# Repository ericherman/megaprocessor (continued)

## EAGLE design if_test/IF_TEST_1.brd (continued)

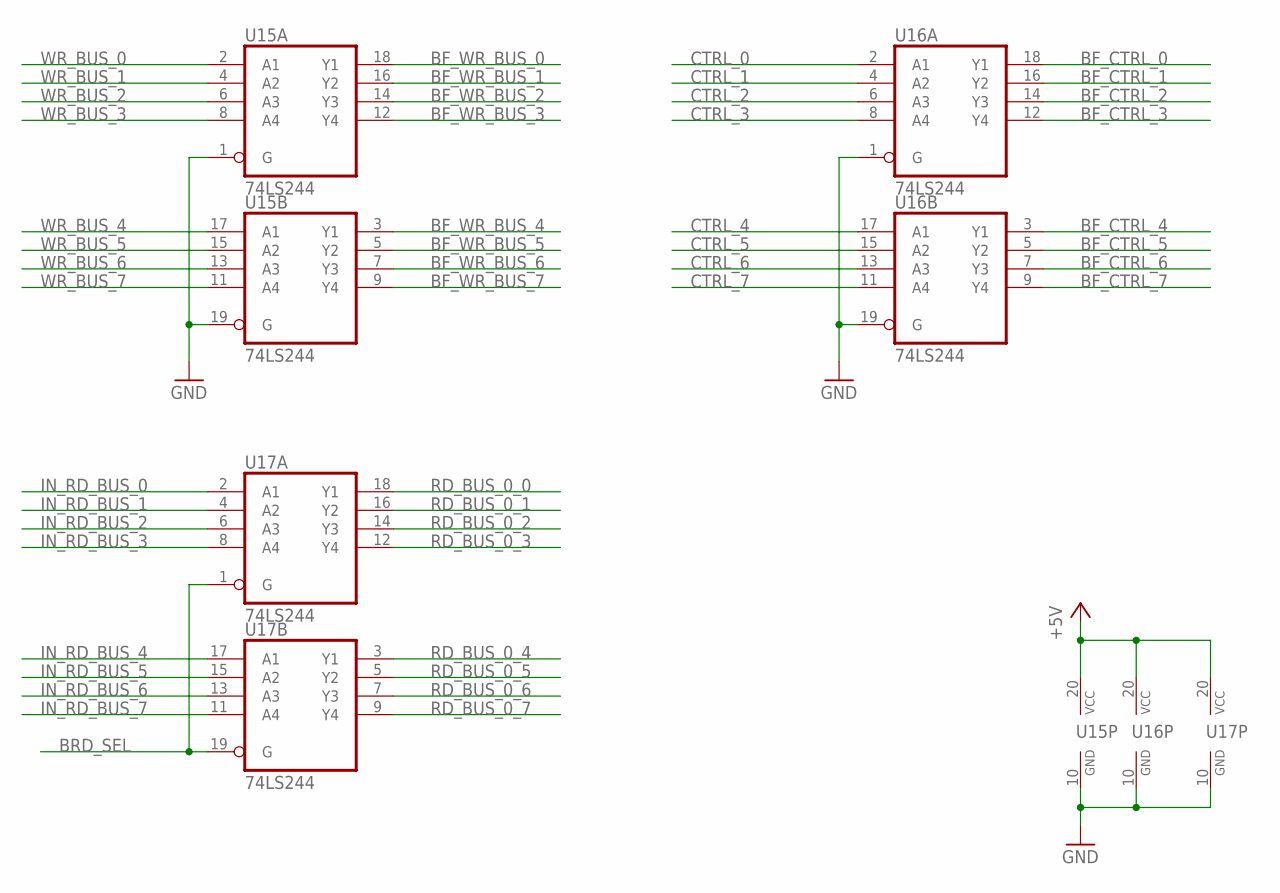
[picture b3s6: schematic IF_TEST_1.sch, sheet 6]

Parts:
U15, U16, U17: 74LS244; DIP20

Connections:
+5V: U15.20 (VCC), U16.20 (VCC), U17.20 (VCC); also elsewhere on the board
BF_CTRL_0: U16.18 (Y1); also elsewhere on the board
BF_CTRL_1: U16.16 (Y2); also elsewhere on the board
BF_CTRL_2: U16.14 (Y3); also elsewhere on the board
BF_CTRL_3: U16.12 (Y4); also elsewhere on the board
BF_CTRL_4: U16.3 (Y1); also elsewhere on the board
BF_CTRL_5: U16.5 (Y2); also elsewhere on the board
BF_CTRL_6: U16.7 (Y3); also elsewhere on the board
BF_CTRL_7: U16.9 (Y4); also elsewhere on the board
BF_WR_BUS_0: U15.18 (Y1); also elsewhere on the board
BF_WR_BUS_1: U15.16 (Y2); also elsewhere on the board
BF_WR_BUS_2: U15.14 (Y3); also elsewhere on the board
BF_WR_BUS_3: U15.12 (Y4); also elsewhere on the board
BF_WR_BUS_4: U15.3 (Y1); also elsewhere on the board
BF_WR_BUS_5: U15.5 (Y2); also elsewhere on the board
BF_WR_BUS_6: U15.7 (Y3); also elsewhere on the board
BF_WR_BUS_7: U15.9 (Y4); also elsewhere on the board
BRD_SEL: U17.1 (G), U17.19 (G); also elsewhere on the board
CTRL_0: U16.2 (A1); also elsewhere on the board
CTRL_1: U16.4 (A2); also elsewhere on the board
CTRL_2: U16.6 (A3); also elsewhere on the board
CTRL_3: U16.8 (A4); also elsewhere on the board
CTRL_4: U16.17 (A1); also elsewhere on the board
CTRL_5: U16.15 (A2); also elsewhere on the board
CTRL_6: U16.13 (A3); also elsewhere on the board
CTRL_7: U16.11 (A4); also elsewhere on the board
GND: U15.1 (G), U15.10 (GND), U15.19 (G), U16.1 (G), U16.10 (GND), U16.19 (G), U17.10 (GND); also elsewhere on the board
IN_RD_BUS_0: U17.2 (A1); also elsewhere on the board
IN_RD_BUS_1: U17.4 (A2); also elsewhere on the board
IN_RD_BUS_2: U17.6 (A3); also elsewhere on the board
IN_RD_BUS_3: U17.8 (A4); also elsewhere on the board
IN_RD_BUS_4: U17.17 (A1); also elsewhere on the board
IN_RD_BUS_5: U17.15 (A2); also elsewhere on the board
IN_RD_BUS_6: U17.13 (A3); also elsewhere on the board
IN_RD_BUS_7: U17.11 (A4); also elsewhere on the board
RD_BUS_0_0: U17.18 (Y1); also elsewhere on the board
RD_BUS_0_1: U17.16 (Y2); also elsewhere on the board
RD_BUS_0_2: U17.14 (Y3); also elsewhere on the board
RD_BUS_0_3: U17.12 (Y4); also elsewhere on the board
RD_BUS_0_4: U17.3 (Y1); also elsewhere on the board
RD_BUS_0_5: U17.5 (Y2); also elsewhere on the board
RD_BUS_0_6: U17.7 (Y3); also elsewhere on the board
RD_BUS_0_7: U17.9 (Y4); also elsewhere on the board
WR_BUS_0: U15.2 (A1); also elsewhere on the board
WR_BUS_1: U15.4 (A2); also elsewhere on the board
WR_BUS_2: U15.6 (A3); also elsewhere on the board
WR_BUS_3: U15.8 (A4); also elsewhere on the board
WR_BUS_4: U15.17 (A1); also elsewhere on the board
WR_BUS_5: U15.15 (A2); also elsewhere on the board
WR_BUS_6: U15.13 (A3); also elsewhere on the board
WR_BUS_7: U15.11 (A4); also elsewhere on the board

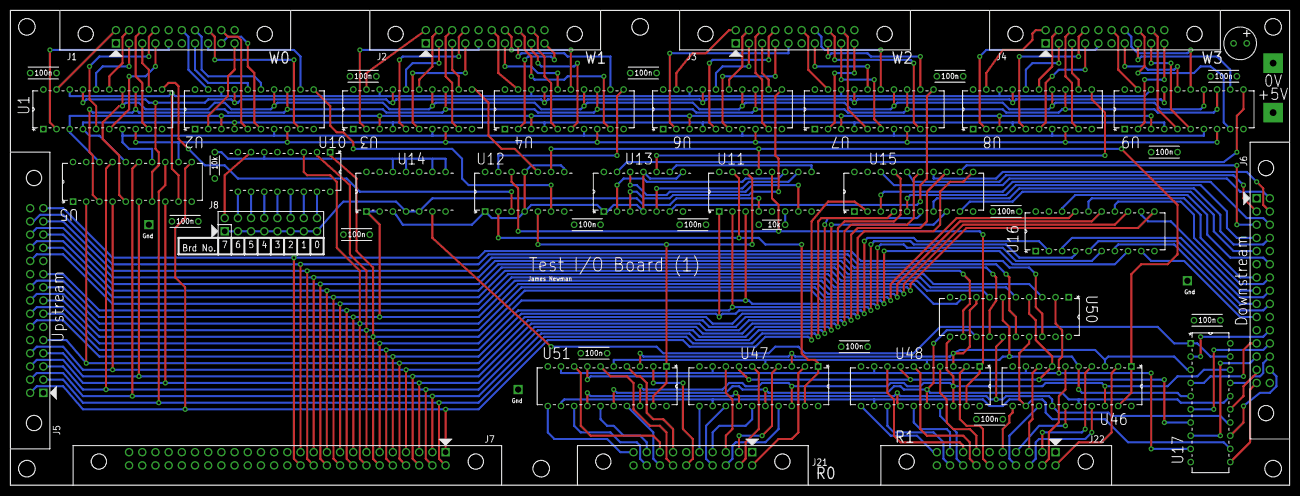
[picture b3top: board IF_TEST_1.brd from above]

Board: 4 copper layers, 246.4 x 91.4 mm, 61 parts (0 on the bottom side), 191 nets.

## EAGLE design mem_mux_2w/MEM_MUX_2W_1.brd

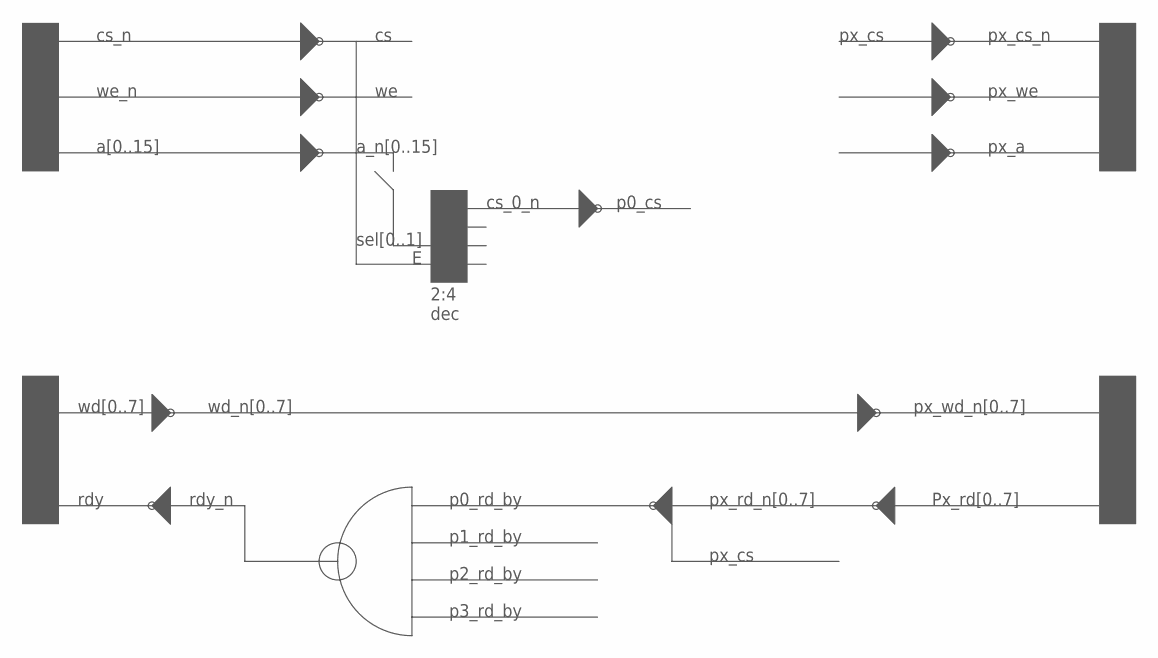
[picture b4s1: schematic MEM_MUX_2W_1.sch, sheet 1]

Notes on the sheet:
cs_n
we_n
a[0..15]
a_n[0..15]
2:4 dec
cs_0_n
p0_cs
sel[0..1]
px_a
px_we
px_cs
px_cs_n
wd[0..7]
wd_n[0..7]
px_wd_n[0..7]
Px_rd[0..7]
px_rd_n[0..7]
p0_rd_by
p1_rd_by
p2_rd_by
p3_rd_by
rdy_n
rdy

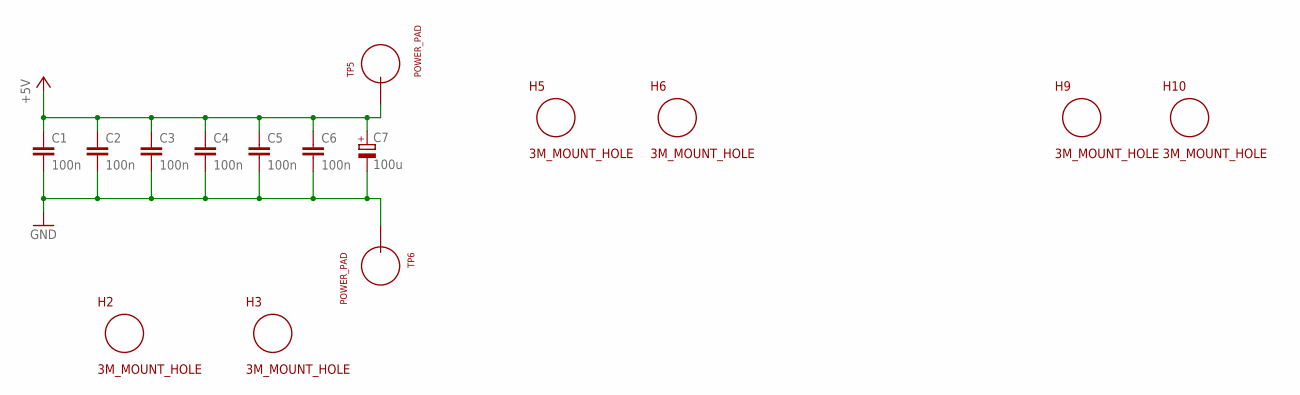
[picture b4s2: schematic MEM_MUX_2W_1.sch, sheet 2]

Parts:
C1, C2, C3, C4, C5, C6: 100n; CAP_P2INCH
C7: 100u; POLARISED_CAP_2P5_6P3MM
H2, H3, H5, H6, H9, H10: 3M_MOUNT_HOLE; 3M_HOLE
TP5, TP6: POWER_PAD

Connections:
+5V: C1.1, C2.1, C3.1, C4.1, C5.1, C6.1, C7.A, TP5.1; also elsewhere on the board
GND: C1.2, C2.2, C3.2, C4.2, C5.2, C6.2, C7.K, TP6.1; also elsewhere on the board

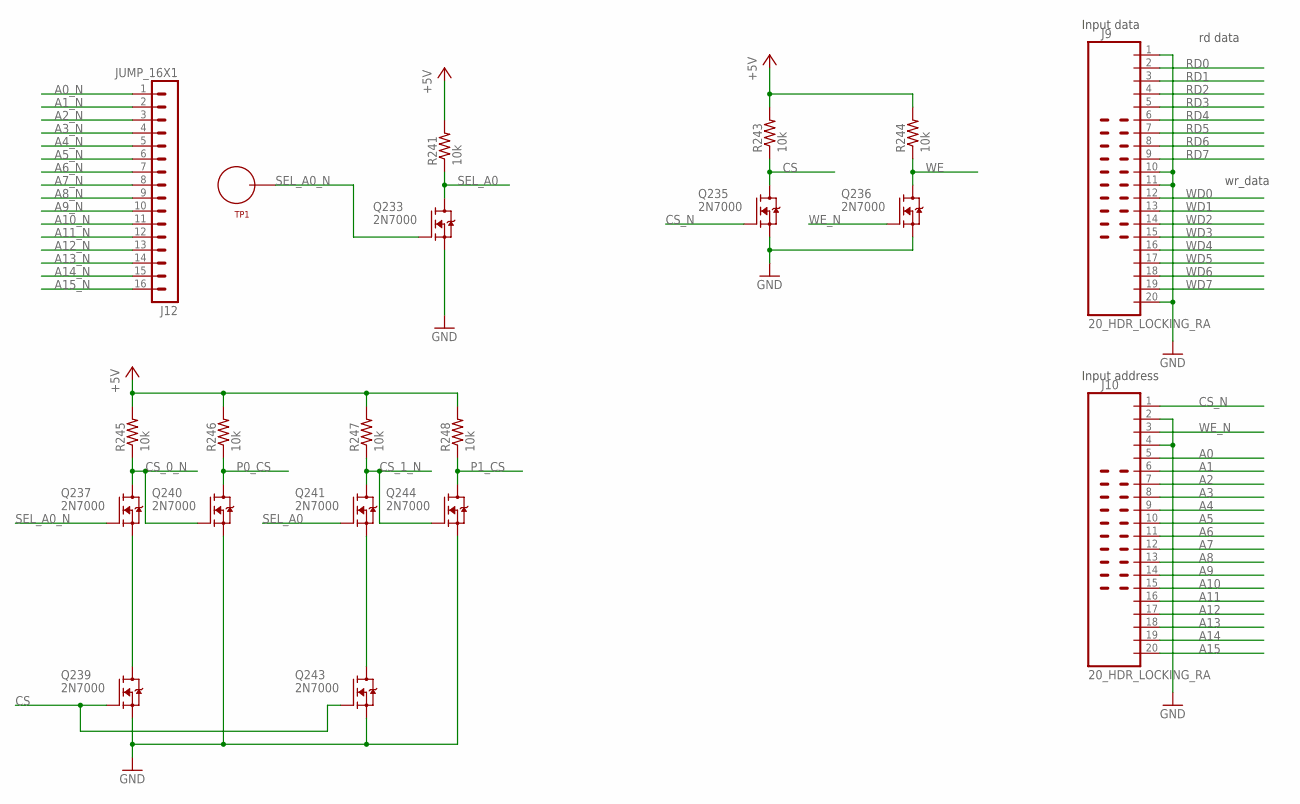
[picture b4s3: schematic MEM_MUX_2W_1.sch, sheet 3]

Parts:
J9, J10: 20_HDR_LOCKING_RA
J12: JUMP_16X1
Q233, Q235, Q236, Q237, Q239, Q240, Q241, Q243, Q244: 2N7000; TO92-DGS
R241, R243, R244, R245, R246, R247, R248: 10k; R_P2INCH
TP1: TEST_LOOP

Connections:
+5V: R241.2, R243.2, R244.2, R245.2, R246.2, R247.2, R248.2; also elsewhere on the board
A0: J10.5; also elsewhere on the board
A0_N: J12.1; also elsewhere on the board
A1: J10.6; also elsewhere on the board
A1_N: J12.2; also elsewhere on the board
A2: J10.7; also elsewhere on the board
A2_N: J12.3; also elsewhere on the board
A3: J10.8; also elsewhere on the board
A3_N: J12.4; also elsewhere on the board
A4: J10.9; also elsewhere on the board
A4_N: J12.5; also elsewhere on the board
A5: J10.10; also elsewhere on the board
A5_N: J12.6; also elsewhere on the board
A6: J10.11; also elsewhere on the board
A6_N: J12.7; also elsewhere on the board
A7: J10.12; also elsewhere on the board
A7_N: J12.8; also elsewhere on the board
A8: J10.13; also elsewhere on the board
A8_N: J12.9; also elsewhere on the board
A9: J10.14; also elsewhere on the board
A9_N: J12.10; also elsewhere on the board
A10: J10.15; also elsewhere on the board
A10_N: J12.11; also elsewhere on the board
A11: J10.16; also elsewhere on the board
A11_N: J12.12; also elsewhere on the board
A12: J10.17; also elsewhere on the board
A12_N: J12.13; also elsewhere on the board
A13: J10.18; also elsewhere on the board
A13_N: J12.14; also elsewhere on the board
A14: J10.19; also elsewhere on the board
A14_N: J12.15; also elsewhere on the board
A15: J10.20; also elsewhere on the board
A15_N: J12.16; also elsewhere on the board
CS: Q235.D, Q239.G, Q243.G, R243.1
CS_0_N: Q237.D, Q240.G, R245.1; also elsewhere on the board
CS_1_N: Q241.D, Q244.G, R247.1; also elsewhere on the board
CS_N: J10.1, Q235.G
GND: J9.1, J9.10, J9.11, J9.20, J10.2, J10.4, Q233.S, Q235.S, Q236.S, Q239.S, Q240.S, Q243.S, Q244.S; also elsewhere on the board
unnamed: Q237.S, Q239.D
unnamed: Q241.S, Q243.D
P0_CS: Q240.D, R246.1; also elsewhere on the board
P1_CS: Q244.D, R248.1; also elsewhere on the board
RD0: J9.2; also elsewhere on the board
RD1: J9.3; also elsewhere on the board
RD2: J9.4; also elsewhere on the board
RD3: J9.5; also elsewhere on the board
RD4: J9.6; also elsewhere on the board
RD5: J9.7; also elsewhere on the board
RD6: J9.8; also elsewhere on the board
RD7: J9.9; also elsewhere on the board
SEL_A0: Q233.D, Q241.G, R241.1
SEL_A0_N: Q233.G, Q237.G, TP1.P$1
WD0: J9.12; also elsewhere on the board
WD1: J9.13; also elsewhere on the board
WD2: J9.14; also elsewhere on the board
WD3: J9.15; also elsewhere on the board
WD4: J9.16; also elsewhere on the board
WD5: J9.17; also elsewhere on the board
WD6: J9.18; also elsewhere on the board
WD7: J9.19; also elsewhere on the board
WE: Q236.D, R244.1; also elsewhere on the board
WE_N: J10.3, Q236.G

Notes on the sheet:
Input data
Input address
rd data
wr_data

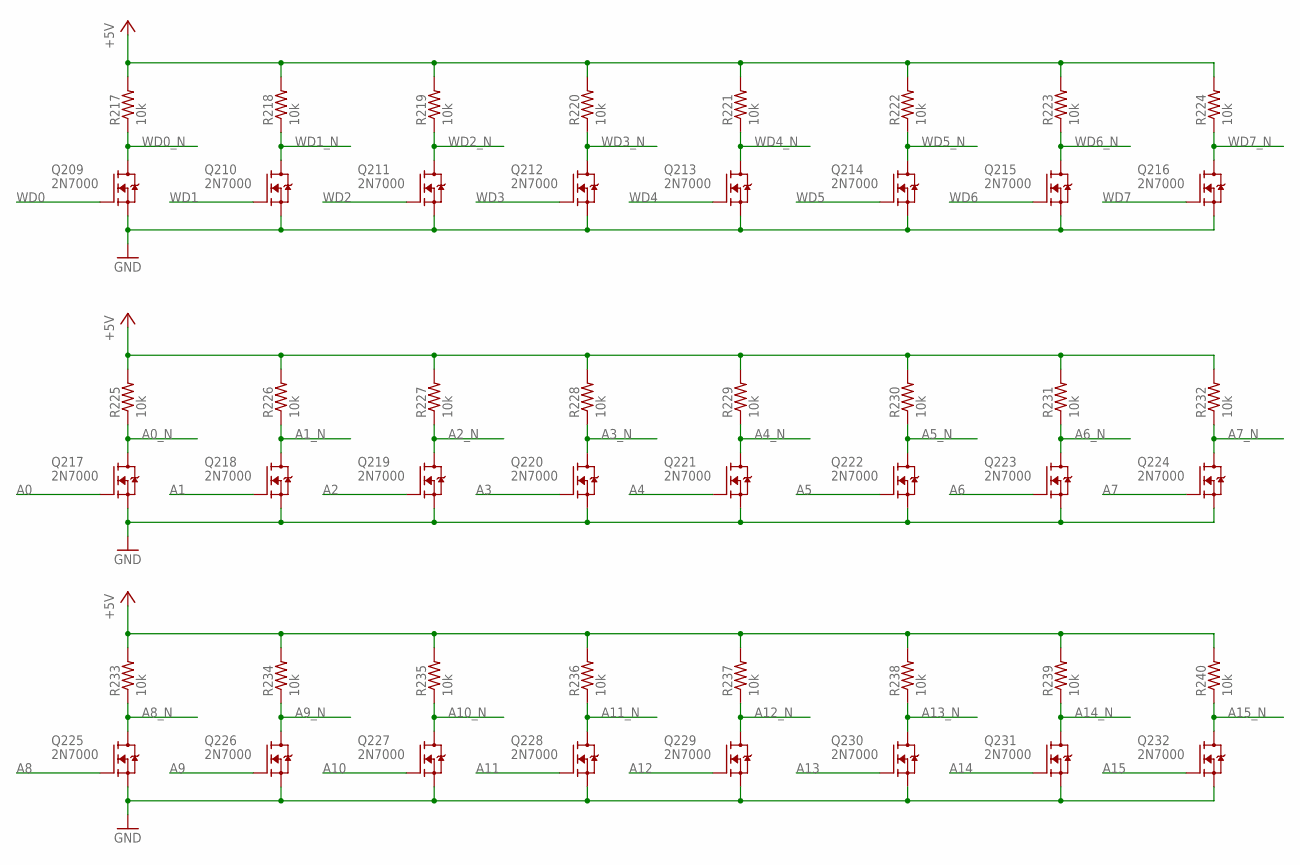
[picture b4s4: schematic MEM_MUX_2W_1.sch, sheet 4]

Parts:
Q209, Q210, Q211, Q212, Q213, Q214, Q215, Q216, Q217, Q218, Q219, Q220, Q221, Q222, Q223, Q224, Q225, Q226, Q227, Q228, Q229, Q230, Q231, Q232: 2N7000; TO92-DGS
R217, R218, R219, R220, R221, R222, R223, R224, R225, R226, R227, R228, R229, R230, R231, R232, R233, R234, R235, R236, R237, R238, R239, R240: 10k; R_P2INCH

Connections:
+5V: R217.2, R218.2, R219.2, R220.2, R221.2, R222.2, R223.2, R224.2, R225.2, R226.2, R227.2, R228.2, R229.2, R230.2, R231.2, R232.2, R233.2, R234.2, R235.2, R236.2, R237.2, R238.2, R239.2, R240.2; also elsewhere on the board
A0: Q217.G; also elsewhere on the board
A0_N: Q217.D, R225.1; also elsewhere on the board
A1: Q218.G; also elsewhere on the board
A1_N: Q218.D, R226.1; also elsewhere on the board
A2: Q219.G; also elsewhere on the board
A2_N: Q219.D, R227.1; also elsewhere on the board
A3: Q220.G; also elsewhere on the board
A3_N: Q220.D, R228.1; also elsewhere on the board
A4: Q221.G; also elsewhere on the board
A4_N: Q221.D, R229.1; also elsewhere on the board
A5: Q222.G; also elsewhere on the board
A5_N: Q222.D, R230.1; also elsewhere on the board
A6: Q223.G; also elsewhere on the board
A6_N: Q223.D, R231.1; also elsewhere on the board
A7: Q224.G; also elsewhere on the board
A7_N: Q224.D, R232.1; also elsewhere on the board
A8: Q225.G; also elsewhere on the board
A8_N: Q225.D, R233.1; also elsewhere on the board
A9: Q226.G; also elsewhere on the board
A9_N: Q226.D, R234.1; also elsewhere on the board
A10: Q227.G; also elsewhere on the board
A10_N: Q227.D, R235.1; also elsewhere on the board
A11: Q228.G; also elsewhere on the board
A11_N: Q228.D, R236.1; also elsewhere on the board
A12: Q229.G; also elsewhere on the board
A12_N: Q229.D, R237.1; also elsewhere on the board
A13: Q230.G; also elsewhere on the board
A13_N: Q230.D, R238.1; also elsewhere on the board
A14: Q231.G; also elsewhere on the board
A14_N: Q231.D, R239.1; also elsewhere on the board
A15: Q232.G; also elsewhere on the board
A15_N: Q232.D, R240.1; also elsewhere on the board
GND: Q209.S, Q210.S, Q211.S, Q212.S, Q213.S, Q214.S, Q215.S, Q216.S, Q217.S, Q218.S, Q219.S, Q220.S, Q221.S, Q222.S, Q223.S, Q224.S, Q225.S, Q226.S, Q227.S, Q228.S, Q229.S, Q230.S, Q231.S, Q232.S; also elsewhere on the board
WD0: Q209.G; also elsewhere on the board
WD0_N: Q209.D, R217.1; also elsewhere on the board
WD1: Q210.G; also elsewhere on the board
WD1_N: Q210.D, R218.1; also elsewhere on the board
WD2: Q211.G; also elsewhere on the board
WD2_N: Q211.D, R219.1; also elsewhere on the board
WD3: Q212.G; also elsewhere on the board
WD3_N: Q212.D, R220.1; also elsewhere on the board
WD4: Q213.G; also elsewhere on the board
WD4_N: Q213.D, R221.1; also elsewhere on the board
WD5: Q214.G; also elsewhere on the board
WD5_N: Q214.D, R222.1; also elsewhere on the board
WD6: Q215.G; also elsewhere on the board
WD6_N: Q215.D, R223.1; also elsewhere on the board
WD7: Q216.G; also elsewhere on the board
WD7_N: Q216.D, R224.1; also elsewhere on the board

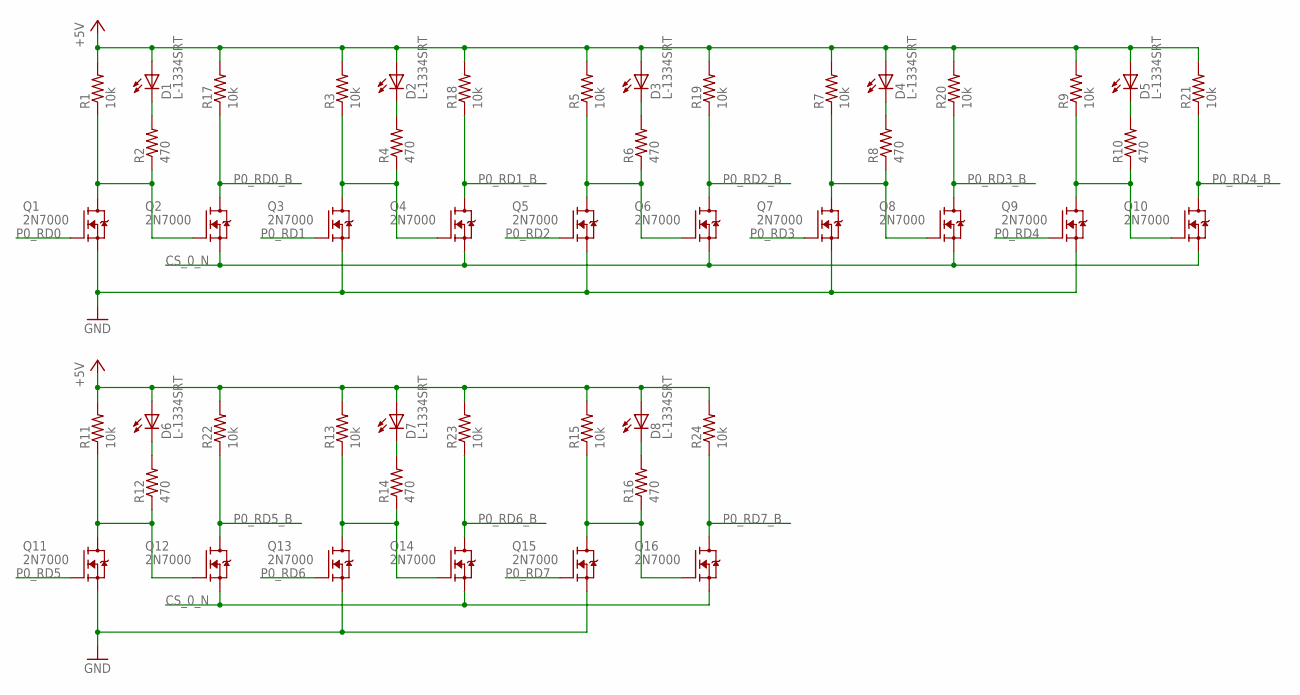
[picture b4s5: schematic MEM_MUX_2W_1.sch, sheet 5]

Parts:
D1, D2, D3, D4, D5, D6, D7, D8: L-1334SRT; LED3MM
Q1, Q2, Q3, Q4, Q5, Q6, Q7, Q8, Q9, Q10, Q11, Q12, Q13, Q14, Q15, Q16: 2N7000; TO92-DGS
R1, R3, R5, R7, R9, R11, R13, R15, R17, R18, R19, R20, R21, R22, R23, R24: 10k; R_P2INCH
R2, R4, R6, R8, R10, R12, R14, R16: 470; R_P2INCH

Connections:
+5V: D1.A, D2.A, D3.A, D4.A, D5.A, D6.A, D7.A, D8.A, R1.2, R3.2, R5.2, R7.2, R9.2, R11.2, R13.2, R15.2, R17.2, R18.2, R19.2, R20.2, R21.2, R22.2, R23.2, R24.2; also elsewhere on the board
CS_0_N: Q2.S, Q4.S, Q6.S, Q8.S, Q10.S, Q12.S, Q14.S, Q16.S; also elsewhere on the board
GND: Q1.S, Q3.S, Q5.S, Q7.S, Q9.S, Q11.S, Q13.S, Q15.S; also elsewhere on the board
unnamed: Q3.D, Q4.G, R3.1, R4.1
unnamed: Q1.D, Q2.G, R1.1, R2.1
unnamed: D1.K (C), R2.2
unnamed: D2.K (C), R4.2
unnamed: Q5.D, Q6.G, R5.1, R6.1
unnamed: D3.K (C), R6.2
unnamed: Q7.D, Q8.G, R7.1, R8.1
unnamed: D4.K (C), R8.2
unnamed: Q9.D, Q10.G, R9.1, R10.1
unnamed: D5.K (C), R10.2
unnamed: Q11.D, Q12.G, R11.1, R12.1
unnamed: D6.K (C), R12.2
unnamed: Q13.D, Q14.G, R13.1, R14.1
unnamed: D7.K (C), R14.2
unnamed: Q15.D, Q16.G, R15.1, R16.1
unnamed: D8.K (C), R16.2
P0_RD0: Q1.G; also elsewhere on the board
P0_RD0_B: Q2.D, R17.1; also elsewhere on the board
P0_RD1: Q3.G; also elsewhere on the board
P0_RD1_B: Q4.D, R18.1; also elsewhere on the board
P0_RD2: Q5.G; also elsewhere on the board
P0_RD2_B: Q6.D, R19.1; also elsewhere on the board
P0_RD3: Q7.G; also elsewhere on the board
P0_RD3_B: Q8.D, R20.1; also elsewhere on the board
P0_RD4: Q9.G; also elsewhere on the board
P0_RD4_B: Q10.D, R21.1; also elsewhere on the board
P0_RD5: Q11.G; also elsewhere on the board
P0_RD5_B: Q12.D, R22.1; also elsewhere on the board
P0_RD6: Q13.G; also elsewhere on the board
P0_RD6_B: Q14.D, R23.1; also elsewhere on the board
P0_RD7: Q15.G; also elsewhere on the board
P0_RD7_B: Q16.D, R24.1; also elsewhere on the board

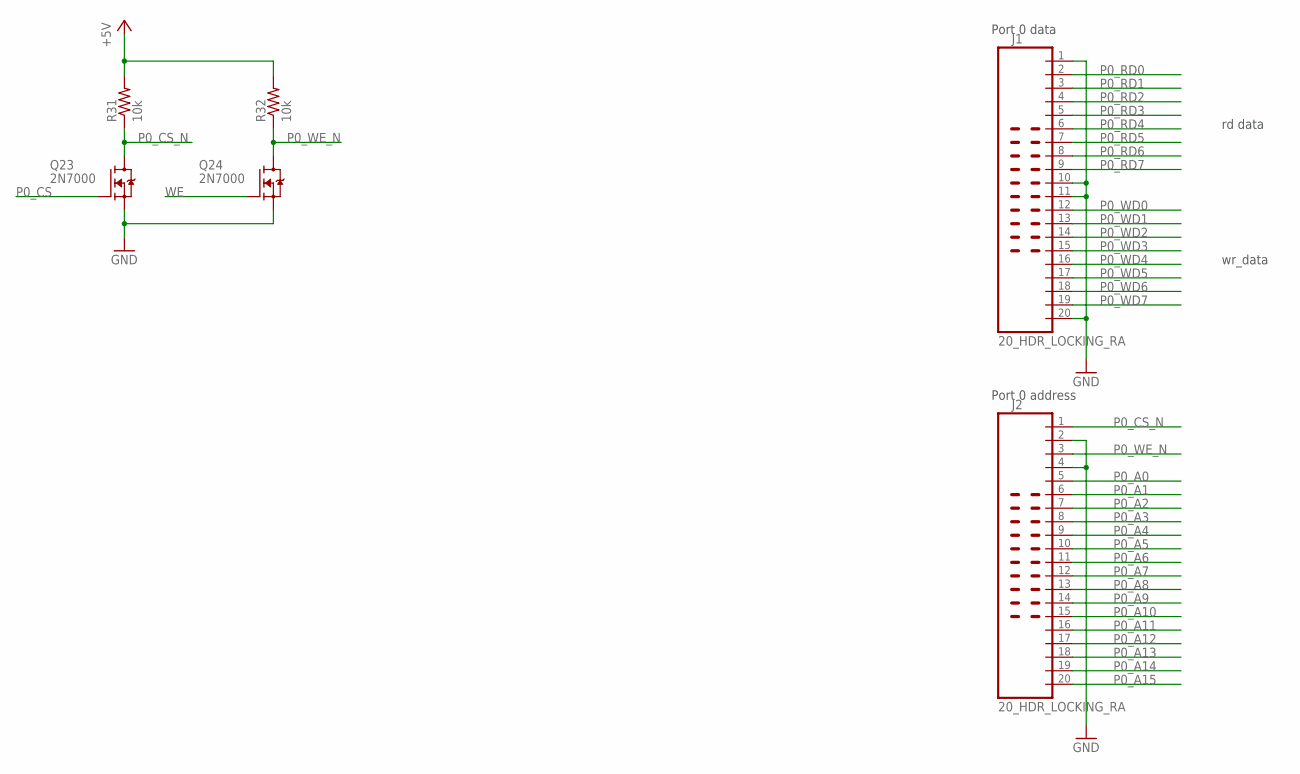
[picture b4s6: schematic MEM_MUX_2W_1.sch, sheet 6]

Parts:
J1, J2: 20_HDR_LOCKING_RA
Q23, Q24: 2N7000; TO92-DGS
R31, R32: 10k; R_P2INCH

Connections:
+5V: R31.2, R32.2; also elsewhere on the board
GND: J1.1, J1.10, J1.11, J1.20, J2.2, J2.4, Q23.S, Q24.S; also elsewhere on the board
P0_A0: J2.5; also elsewhere on the board
P0_A1: J2.6; also elsewhere on the board
P0_A2: J2.7; also elsewhere on the board
P0_A3: J2.8; also elsewhere on the board
P0_A4: J2.9; also elsewhere on the board
P0_A5: J2.10; also elsewhere on the board
P0_A6: J2.11; also elsewhere on the board
P0_A7: J2.12; also elsewhere on the board
P0_A8: J2.13; also elsewhere on the board
P0_A9: J2.14; also elsewhere on the board
P0_A10: J2.15; also elsewhere on the board
P0_A11: J2.16; also elsewhere on the board
P0_A12: J2.17; also elsewhere on the board
P0_A13: J2.18; also elsewhere on the board
P0_A14: J2.19; also elsewhere on the board
P0_A15: J2.20; also elsewhere on the board
P0_CS: Q23.G; also elsewhere on the board
P0_CS_N: J2.1, Q23.D, R31.1
P0_RD0: J1.2; also elsewhere on the board
P0_RD1: J1.3; also elsewhere on the board
P0_RD2: J1.4; also elsewhere on the board
P0_RD3: J1.5; also elsewhere on the board
P0_RD4: J1.6; also elsewhere on the board
P0_RD5: J1.7; also elsewhere on the board
P0_RD6: J1.8; also elsewhere on the board
P0_RD7: J1.9; also elsewhere on the board
P0_WD0: J1.12; also elsewhere on the board
P0_WD1: J1.13; also elsewhere on the board
P0_WD2: J1.14; also elsewhere on the board
P0_WD3: J1.15; also elsewhere on the board
P0_WD4: J1.16; also elsewhere on the board
P0_WD5: J1.17; also elsewhere on the board
P0_WD6: J1.18; also elsewhere on the board
P0_WD7: J1.19; also elsewhere on the board
P0_WE_N: J2.3, Q24.D, R32.1
WE: Q24.G; also elsewhere on the board

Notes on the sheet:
Port 0 data
Port 0 address
rd data
wr_data

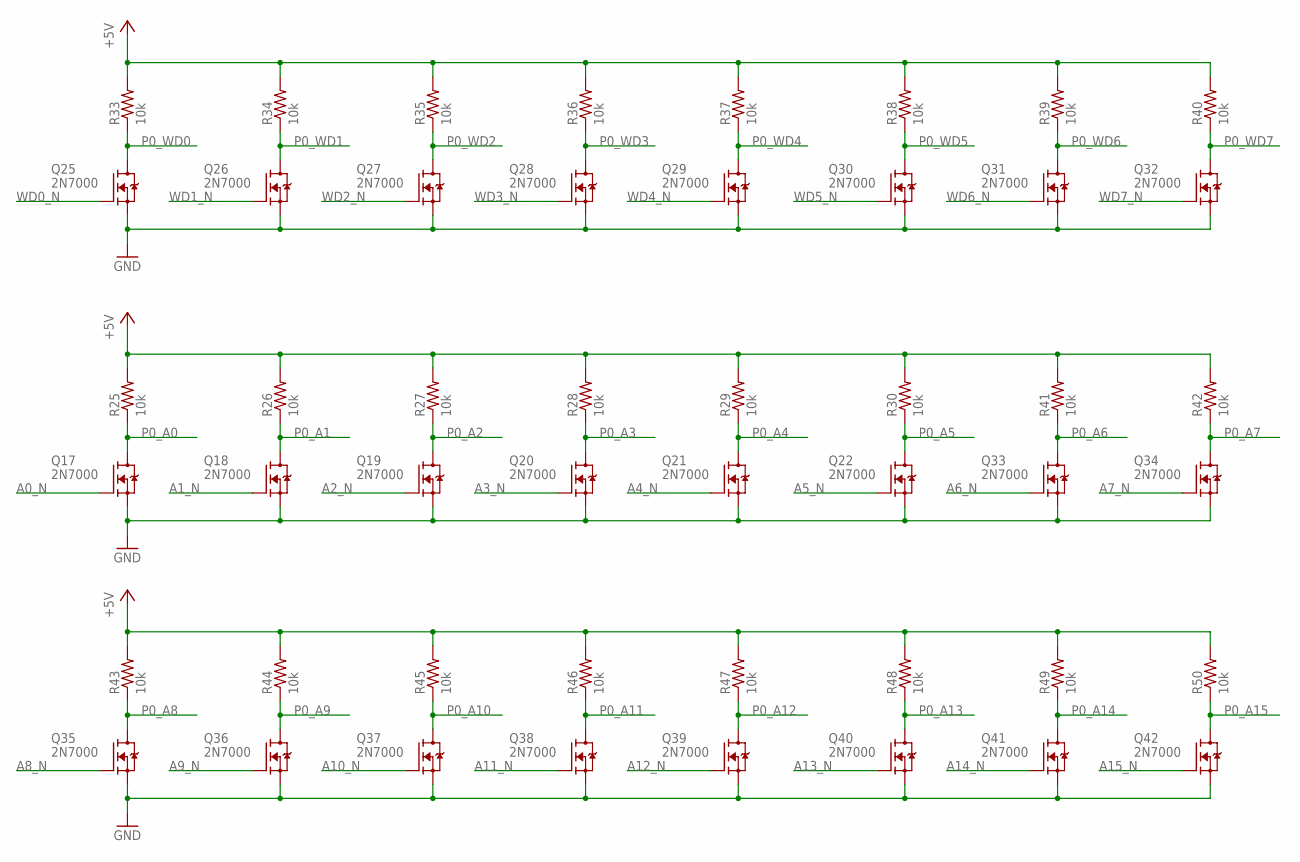
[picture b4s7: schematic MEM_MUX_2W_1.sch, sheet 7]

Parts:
Q17, Q18, Q19, Q20, Q21, Q22, Q25, Q26, Q27, Q28, Q29, Q30, Q31, Q32, Q33, Q34, Q35, Q36, Q37, Q38, Q39, Q40, Q41, Q42: 2N7000; TO92-DGS
R25, R26, R27, R28, R29, R30, R33, R34, R35, R36, R37, R38, R39, R40, R41, R42, R43, R44, R45, R46, R47, R48, R49, R50: 10k; R_P2INCH

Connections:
+5V: R25.2, R26.2, R27.2, R28.2, R29.2, R30.2, R33.2, R34.2, R35.2, R36.2, R37.2, R38.2, R39.2, R40.2, R41.2, R42.2, R43.2, R44.2, R45.2, R46.2, R47.2, R48.2, R49.2, R50.2; also elsewhere on the board
A0_N: Q17.G; also elsewhere on the board
A1_N: Q18.G; also elsewhere on the board
A2_N: Q19.G; also elsewhere on the board
A3_N: Q20.G; also elsewhere on the board
A4_N: Q21.G; also elsewhere on the board
A5_N: Q22.G; also elsewhere on the board
A6_N: Q33.G; also elsewhere on the board
A7_N: Q34.G; also elsewhere on the board
A8_N: Q35.G; also elsewhere on the board
A9_N: Q36.G; also elsewhere on the board
A10_N: Q37.G; also elsewhere on the board
A11_N: Q38.G; also elsewhere on the board
A12_N: Q39.G; also elsewhere on the board
A13_N: Q40.G; also elsewhere on the board
A14_N: Q41.G; also elsewhere on the board
A15_N: Q42.G; also elsewhere on the board
GND: Q17.S, Q18.S, Q19.S, Q20.S, Q21.S, Q22.S, Q25.S, Q26.S, Q27.S, Q28.S, Q29.S, Q30.S, Q31.S, Q32.S, Q33.S, Q34.S, Q35.S, Q36.S, Q37.S, Q38.S, Q39.S, Q40.S, Q41.S, Q42.S; also elsewhere on the board
P0_A0: Q17.D, R25.1; also elsewhere on the board
P0_A1: Q18.D, R26.1; also elsewhere on the board
P0_A2: Q19.D, R27.1; also elsewhere on the board
P0_A3: Q20.D, R28.1; also elsewhere on the board
P0_A4: Q21.D, R29.1; also elsewhere on the board
P0_A5: Q22.D, R30.1; also elsewhere on the board
P0_A6: Q33.D, R41.1; also elsewhere on the board
P0_A7: Q34.D, R42.1; also elsewhere on the board
P0_A8: Q35.D, R43.1; also elsewhere on the board
P0_A9: Q36.D, R44.1; also elsewhere on the board
P0_A10: Q37.D, R45.1; also elsewhere on the board
P0_A11: Q38.D, R46.1; also elsewhere on the board
P0_A12: Q39.D, R47.1; also elsewhere on the board
P0_A13: Q40.D, R48.1; also elsewhere on the board
P0_A14: Q41.D, R49.1; also elsewhere on the board
P0_A15: Q42.D, R50.1; also elsewhere on the board
P0_WD0: Q25.D, R33.1; also elsewhere on the board
P0_WD1: Q26.D, R34.1; also elsewhere on the board
P0_WD2: Q27.D, R35.1; also elsewhere on the board
P0_WD3: Q28.D, R36.1; also elsewhere on the board
P0_WD4: Q29.D, R37.1; also elsewhere on the board
P0_WD5: Q30.D, R38.1; also elsewhere on the board
P0_WD6: Q31.D, R39.1; also elsewhere on the board
P0_WD7: Q32.D, R40.1; also elsewhere on the board
WD0_N: Q25.G; also elsewhere on the board
WD1_N: Q26.G; also elsewhere on the board
WD2_N: Q27.G; also elsewhere on the board
WD3_N: Q28.G; also elsewhere on the board
WD4_N: Q29.G; also elsewhere on the board
WD5_N: Q30.G; also elsewhere on the board
WD6_N: Q31.G; also elsewhere on the board
WD7_N: Q32.G; also elsewhere on the board

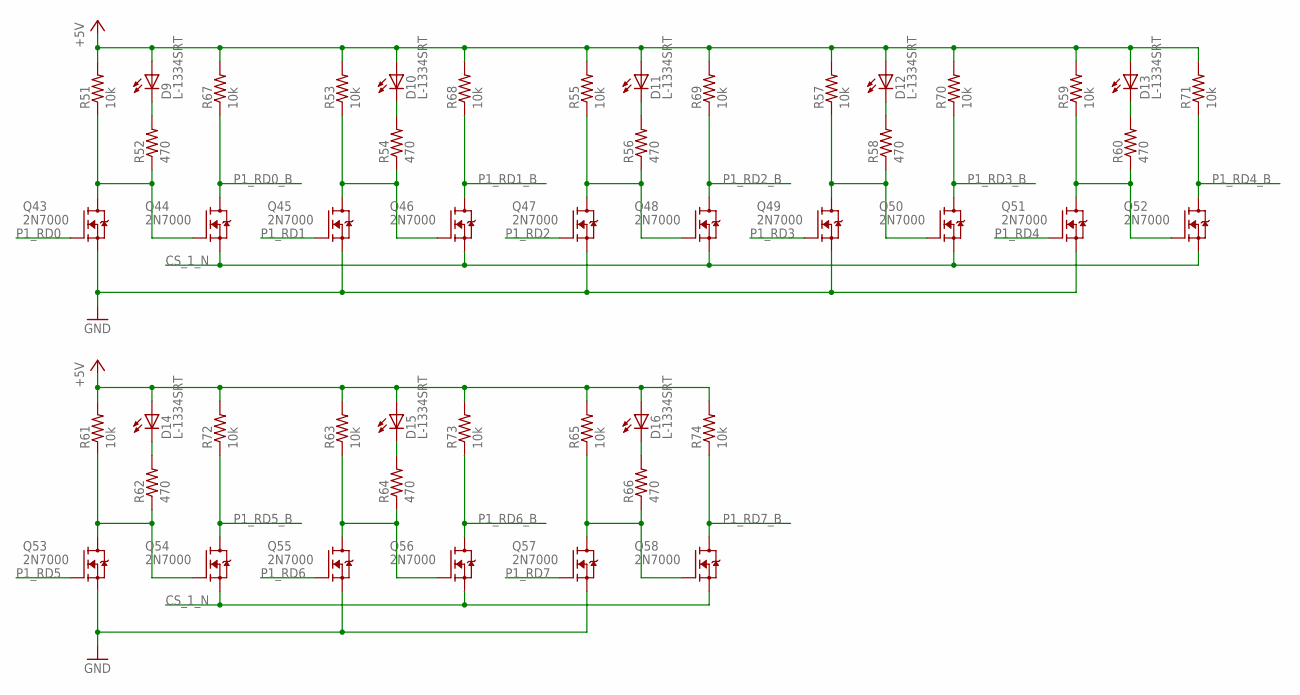
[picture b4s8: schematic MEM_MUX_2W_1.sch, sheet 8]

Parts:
D9, D10, D11, D12, D13, D14, D15, D16: L-1334SRT; LED3MM
Q43, Q44, Q45, Q46, Q47, Q48, Q49, Q50, Q51, Q52, Q53, Q54, Q55, Q56, Q57, Q58: 2N7000; TO92-DGS
R51, R53, R55, R57, R59, R61, R63, R65, R67, R68, R69, R70, R71, R72, R73, R74: 10k; R_P2INCH
R52, R54, R56, R58, R60, R62, R64, R66: 470; R_P2INCH

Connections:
+5V: D9.A, D10.A, D11.A, D12.A, D13.A, D14.A, D15.A, D16.A, R51.2, R53.2, R55.2, R57.2, R59.2, R61.2, R63.2, R65.2, R67.2, R68.2, R69.2, R70.2, R71.2, R72.2, R73.2, R74.2; also elsewhere on the board
CS_1_N: Q44.S, Q46.S, Q48.S, Q50.S, Q52.S, Q54.S, Q56.S, Q58.S; also elsewhere on the board
GND: Q43.S, Q45.S, Q47.S, Q49.S, Q51.S, Q53.S, Q55.S, Q57.S; also elsewhere on the board
unnamed: Q43.D, Q44.G, R51.1, R52.1
unnamed: D9.K (C), R52.2
unnamed: Q45.D, Q46.G, R53.1, R54.1
unnamed: D10.K (C), R54.2
unnamed: Q47.D, Q48.G, R55.1, R56.1
unnamed: D11.K (C), R56.2
unnamed: Q49.D, Q50.G, R57.1, R58.1
unnamed: D12.K (C), R58.2
unnamed: Q51.D, Q52.G, R59.1, R60.1
unnamed: D13.K (C), R60.2
unnamed: Q53.D, Q54.G, R61.1, R62.1
unnamed: D14.K (C), R62.2
unnamed: Q55.D, Q56.G, R63.1, R64.1
unnamed: D15.K (C), R64.2
unnamed: Q57.D, Q58.G, R65.1, R66.1
unnamed: D16.K (C), R66.2
P1_RD0: Q43.G; also elsewhere on the board
P1_RD0_B: Q44.D, R67.1; also elsewhere on the board
P1_RD1: Q45.G; also elsewhere on the board
P1_RD1_B: Q46.D, R68.1; also elsewhere on the board
P1_RD2: Q47.G; also elsewhere on the board
P1_RD2_B: Q48.D, R69.1; also elsewhere on the board
P1_RD3: Q49.G; also elsewhere on the board
P1_RD3_B: Q50.D, R70.1; also elsewhere on the board
P1_RD4: Q51.G; also elsewhere on the board
P1_RD4_B: Q52.D, R71.1; also elsewhere on the board
P1_RD5: Q53.G; also elsewhere on the board
P1_RD5_B: Q54.D, R72.1; also elsewhere on the board
P1_RD6: Q55.G; also elsewhere on the board
P1_RD6_B: Q56.D, R73.1; also elsewhere on the board
P1_RD7: Q57.G; also elsewhere on the board
P1_RD7_B: Q58.D, R74.1; also elsewhere on the board

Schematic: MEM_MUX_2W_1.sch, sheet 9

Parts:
J3, J4: 20_HDR_LOCKING_RA
Q59, Q60: 2N7000; TO92-DGS
R75, R76: 10k; R_P2INCH

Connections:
+5V: R75.2, R76.2; also elsewhere on the board
GND: J3.1, J3.10, J3.11, J3.20, J4.2, J4.4, Q59.S, Q60.S; also elsewhere on the board
P1_A0: J4.5; also elsewhere on the board
P1_A1: J4.6; also elsewhere on the board
P1_A2: J4.7; also elsewhere on the board
P1_A3: J4.8; also elsewhere on the board
P1_A4: J4.9; also elsewhere on the board
P1_A5: J4.10; also elsewhere on the board
P1_A6: J4.11; also elsewhere on the board
P1_A7: J4.12; also elsewhere on the board
P1_A8: J4.13; also elsewhere on the board
P1_A9: J4.14; also elsewhere on the board
P1_A10: J4.15; also elsewhere on the board
P1_A11: J4.16; also elsewhere on the board
P1_A12: J4.17; also elsewhere on the board
P1_A13: J4.18; also elsewhere on the board
P1_A14: J4.19; also elsewhere on the board
P1_A15: J4.20; also elsewhere on the board
P1_CS: Q59.G; also elsewhere on the board
P1_CS_N: J4.1, Q59.D, R75.1
P1_RD0: J3.2; also elsewhere on the board
P1_RD1: J3.3; also elsewhere on the board
P1_RD2: J3.4; also elsewhere on the board
P1_RD3: J3.5; also elsewhere on the board
P1_RD4: J3.6; also elsewhere on the board
P1_RD5: J3.7; also elsewhere on the board
P1_RD6: J3.8; also elsewhere on the board
P1_RD7: J3.9; also elsewhere on the board
P1_WD0: J3.12; also elsewhere on the board
P1_WD1: J3.13; also elsewhere on the board
P1_WD2: J3.14; also elsewhere on the board
P1_WD3: J3.15; also elsewhere on the board
P1_WD4: J3.16; also elsewhere on the board
P1_WD5: J3.17; also elsewhere on the board
P1_WD6: J3.18; also elsewhere on the board
P1_WD7: J3.19; also elsewhere on the board
P1_WE_N: J4.3, Q60.D, R76.1
WE: Q60.G; also elsewhere on the board

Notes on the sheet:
Port 1 data
Port 1 address
rd data
wr_data
